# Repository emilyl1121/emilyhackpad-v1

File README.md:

# emilyhackpad-v1
This is for my hackpad, a macropad project that has 4 keys and basic functions!
The four keys have the following functions
- copy
- paste
- skip audio
- mute

## CAD
Here is the overall design of my case, designed using Fusion:

----
## PCB
Here is the PCB's schematic the PCB itself!

----

## Firmware
For the firmware, I used KMK configuration to change the keys' functions

----
## BOM:

I used these components in the project:
- 1x XIAO RP2040
- 1x Case (2 printed parts)
- 2x SK6812 MINI-E LEDs 
- 4x Blank DSA keycaps

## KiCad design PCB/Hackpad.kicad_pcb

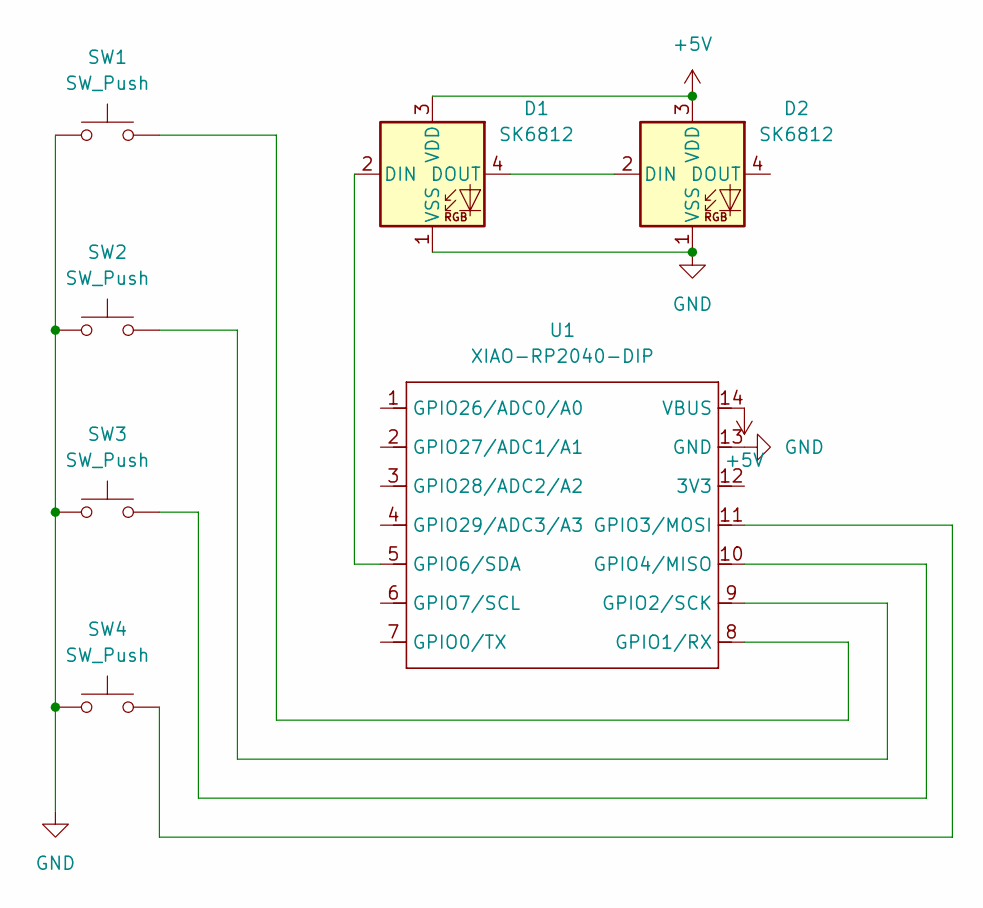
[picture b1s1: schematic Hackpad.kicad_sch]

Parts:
D1, D2: SK6812; LED_SK6812MINI_PLCC4_3.5x3.5mm_P1.75mm
SW1, SW2, SW3, SW4: SW_Push; SW_Cherry_MX_1.00u_PCB
U1: XIAO-RP2040-DIP

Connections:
+5V: D1.3 (VDD), D2.3 (VDD), U1.14 (VBUS)
GND: D1.1 (VSS), D2.1 (VSS), SW1.1, SW2.1, SW3.1, SW4.1, U1.13 (GND)
unnamed: D1.2 (DIN), U1.5 (GPIO6/SDA)
unnamed: D1.4 (DOUT), D2.2 (DIN)
unnamed: SW1.2, U1.8 (GPIO1/RX)
unnamed: SW2.2, U1.9 (GPIO2/SCK)
unnamed: SW4.2, U1.11 (GPIO3/MOSI)
unnamed: SW3.2, U1.10 (GPIO4/MISO)

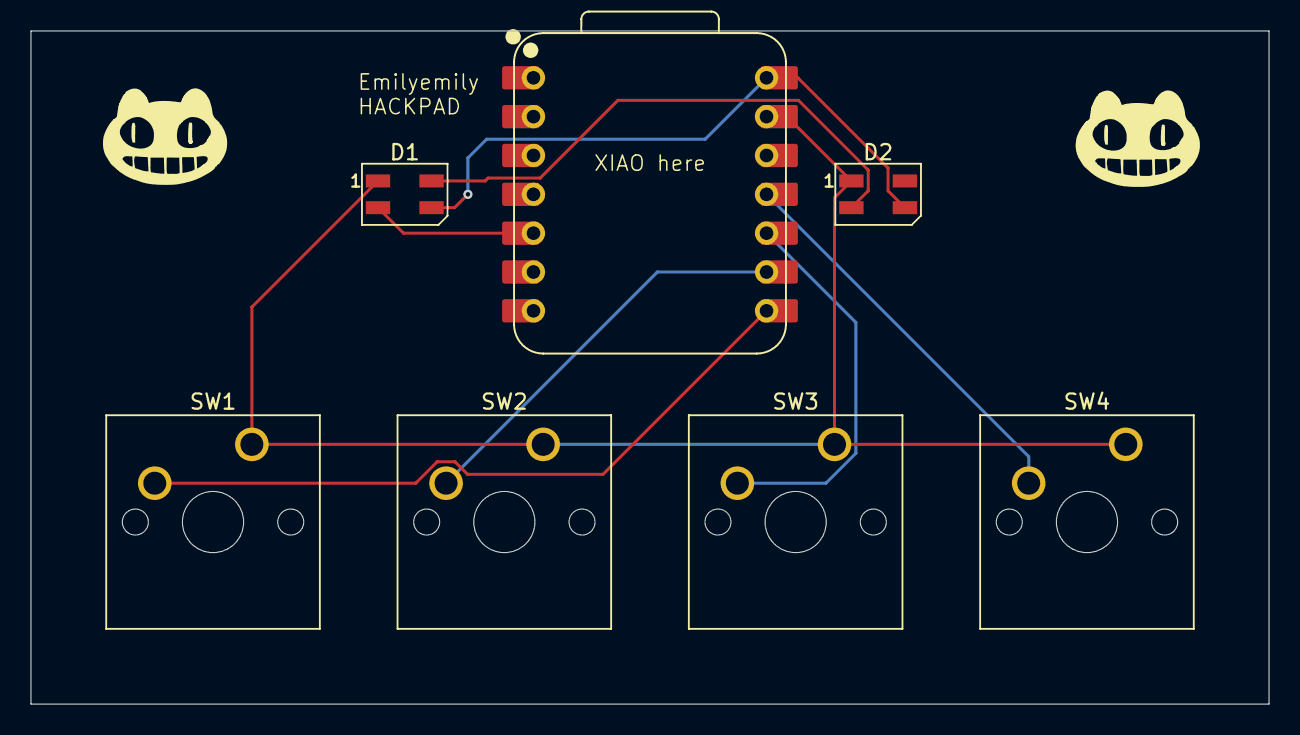
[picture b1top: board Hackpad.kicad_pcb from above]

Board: 2 copper layers, 81.0 x 44.0 mm, 7 parts (0 on the bottom side), 8 nets.

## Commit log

2025-06-11 Create file
2025-06-11 update file
2025-06-11 add firmware doc
